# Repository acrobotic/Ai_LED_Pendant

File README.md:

# Ai_LED_Pendant
# Ai_LED_Pendant

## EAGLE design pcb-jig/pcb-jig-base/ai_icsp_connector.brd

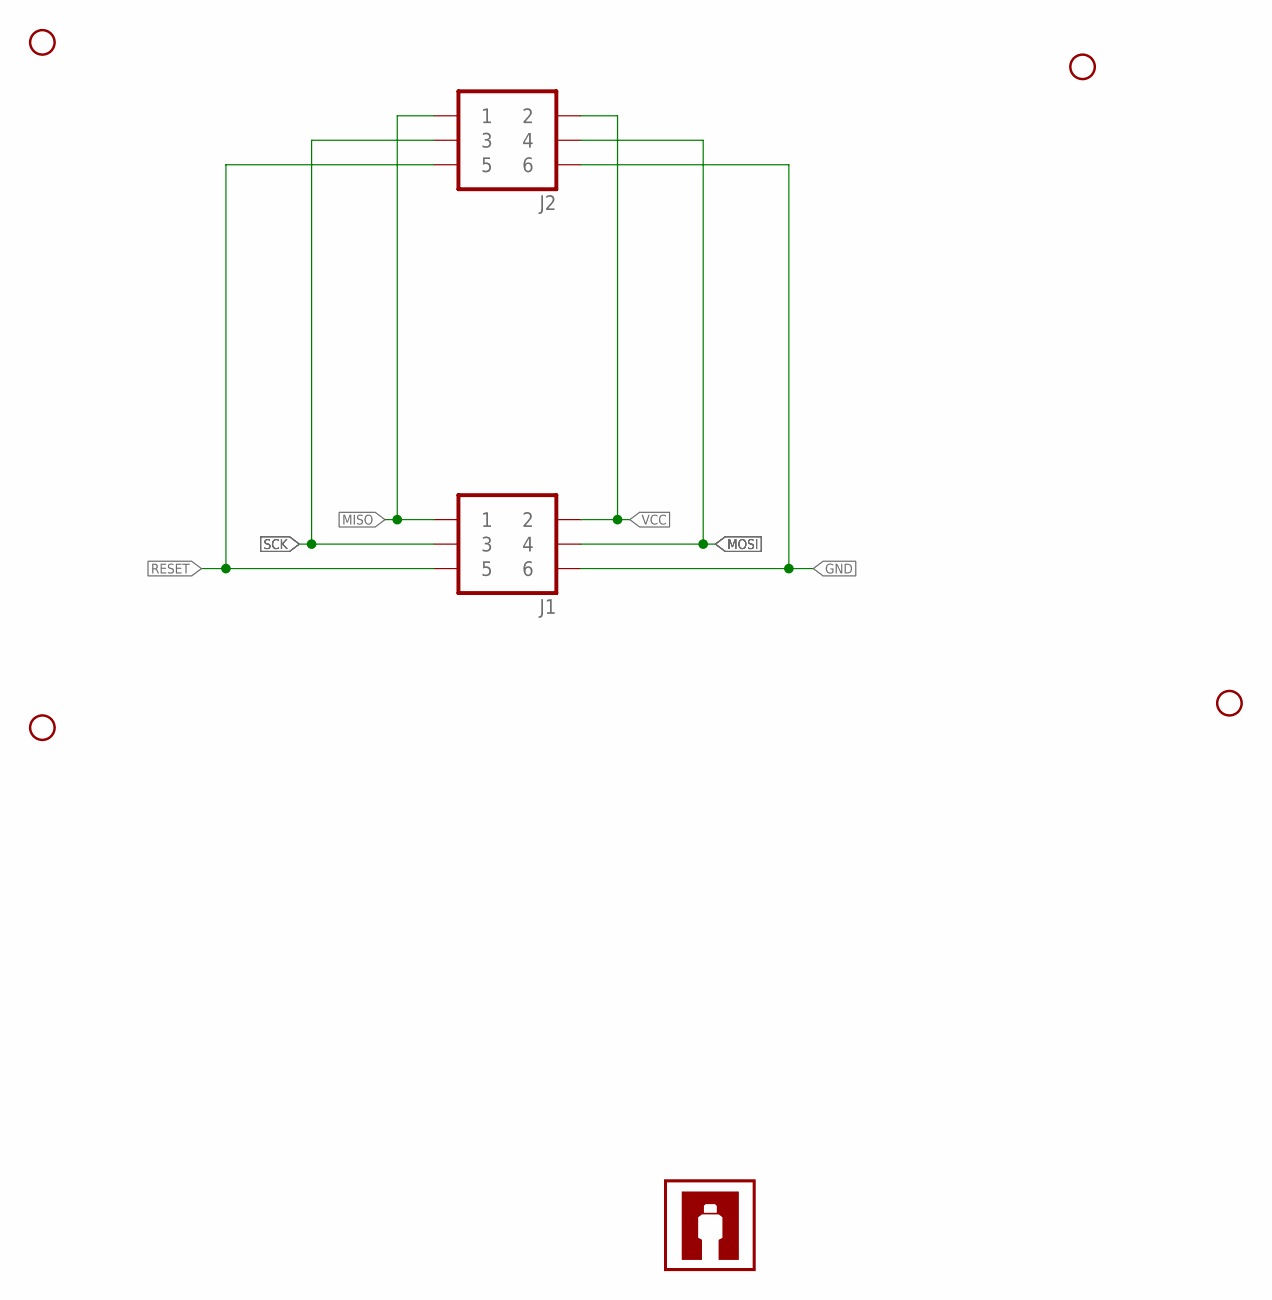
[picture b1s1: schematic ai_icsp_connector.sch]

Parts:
J1: 2X03
J2: 2X032X03-ICSP; 2X03-ICSP
STANDOFF1, STANDOFF2, STANDOFF3, STANDOFF4: STAND-OFF4; STAND-OFF-4
U$1: AI-LOGOXS; AI-LOGO-XS

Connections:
GND: J1.6, J2.6
MISO: J1.1, J2.1
MOSI: J1.4, J2.4
RESET: J1.5, J2.5
SCK: J1.3, J2.3
VCC: J1.2, J2.2

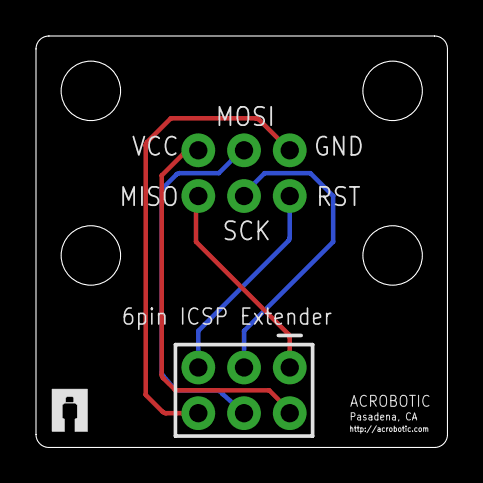
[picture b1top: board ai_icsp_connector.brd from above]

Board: 2 copper layers, 22.9 x 22.9 mm, 7 parts (0 on the bottom side), 6 nets.

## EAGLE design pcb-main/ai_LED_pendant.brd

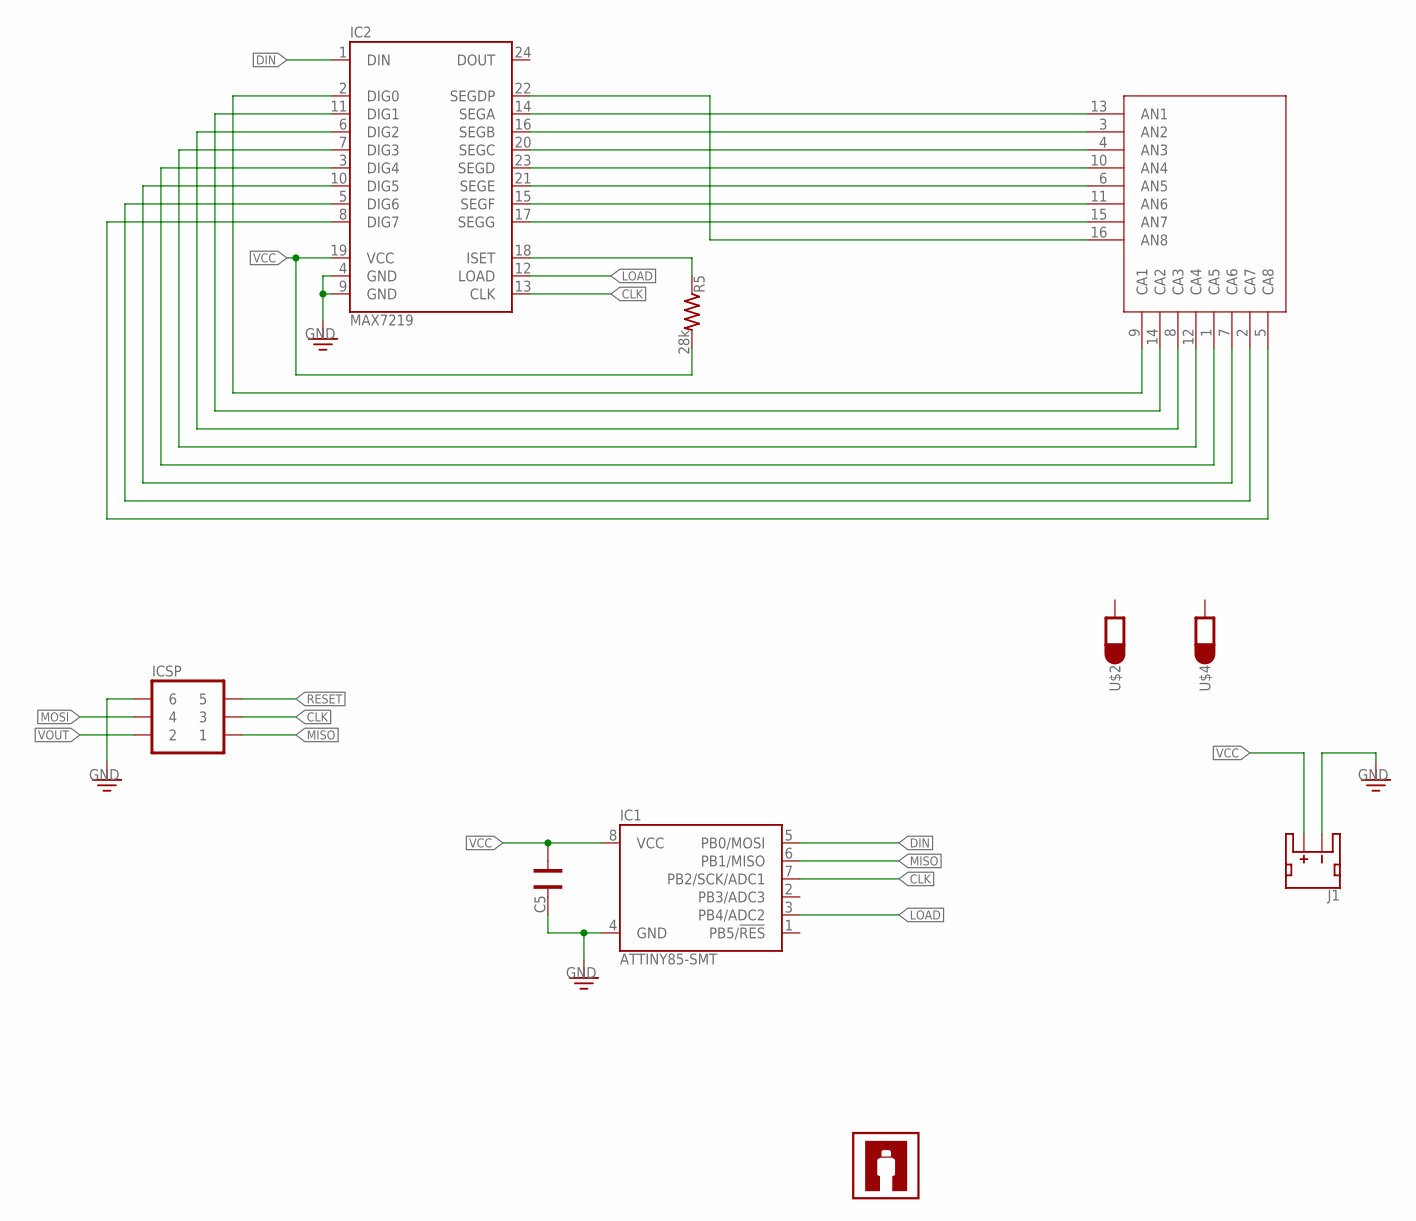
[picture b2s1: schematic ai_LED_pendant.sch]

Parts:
C5: CAP0402; CAP-0402
IC1: ATTINY85-SMT; SO08-EIAJ
IC2: MAX7219-SMD; SOIC24
ICSP: 2X032X03-ICSP-SMALL; 2X03-ICSP-SMALL
J1: JST-2P-MALE; JST-2P-SMD
MATRIX: MATRIX-8X8-SINGLE; LEDM88SMR
R5: 28k; RES-0402
U$1: AI-LOGOXS; AI-LOGO-XS
U$2, U$4: 1X01-PETAL

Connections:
CLK: IC1.7 (PB2/SCK/ADC1), IC2.13 (CLK), ICSP.3
DIG0: IC2.2 (DIG0), MATRIX.9 (CA1)
DIN: IC1.5 (PB0/MOSI), IC2.1 (DIN)
GND: C5.2, IC1.4 (GND), IC2.4 (GND), IC2.9 (GND), ICSP.6, J1.2 (-)
LOAD: IC1.3 (PB4/ADC2), IC2.12 (LOAD)
MISO: IC1.6 (PB1/MISO), ICSP.1
MOSI: ICSP.4
unnamed: IC2.18 (ISET), R5.1
unnamed: IC2.11 (DIG1), MATRIX.14 (CA2)
unnamed: IC2.6 (DIG2), MATRIX.8 (CA3)
unnamed: IC2.7 (DIG3), MATRIX.12 (CA4)
unnamed: IC2.3 (DIG4), MATRIX.1 (CA5)
unnamed: IC2.10 (DIG5), MATRIX.7 (CA6)
unnamed: IC2.5 (DIG6), MATRIX.2 (CA7)
unnamed: IC2.8 (DIG7), MATRIX.5 (CA8)
unnamed: IC2.22 (SEGDP), MATRIX.16 (AN8)
RESET: ICSP.5
SEGA: IC2.14 (SEGA), MATRIX.13 (AN1)
SEGB: IC2.16 (SEGB), MATRIX.3 (AN2)
SEGC: IC2.20 (SEGC), MATRIX.4 (AN3)
SEGD: IC2.23 (SEGD), MATRIX.10 (AN4)
SEGE: IC2.21 (SEGE), MATRIX.6 (AN5)
SEGF: IC2.15 (SEGF), MATRIX.11 (AN6)
SEGG: IC2.17 (SEGG), MATRIX.15 (AN7)
VCC: C5.1, IC1.8 (VCC), IC2.19 (VCC), J1.1 (+), R5.2
VOUT: ICSP.2

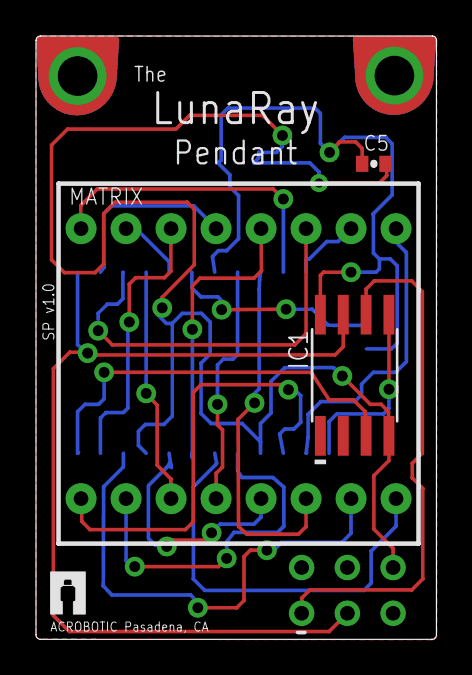
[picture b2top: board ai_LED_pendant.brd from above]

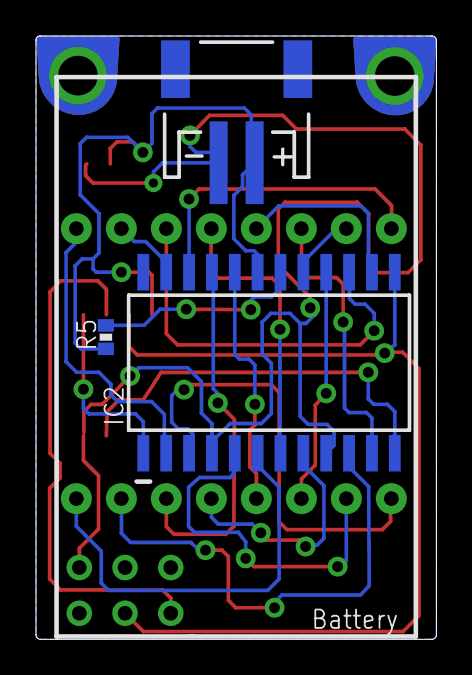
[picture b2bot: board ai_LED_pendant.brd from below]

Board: 2 copper layers, 22.2 x 33.5 mm, 10 parts (3 on the bottom side), 23 nets.

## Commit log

2015-06-03 gerbers added
2015-08-12 merging
